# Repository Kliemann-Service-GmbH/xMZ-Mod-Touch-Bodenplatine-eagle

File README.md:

# xMZ-Mod-Touch
## Eagle Dateien Bodenplatine

## Howto's
### Material Listen (BOM) erstellen

Die Material Listen werden aus den Eagle Zeichnungen gewonnen. Hierzu werden in
Eagle zunächst über den "design link" alle Bauteile in der Farnell Datenbank
gesucht. Anschließend wird diese Liste gespeicherti (Design Link Export).

* Dateiname: "Deckelplatine $VERSION-order.txt"

Danach wird das bom.ulp in Eagle ausgeführt. Folgende Einstellungen sind zu
wählen:

	Listen-Typ: Werte (Häckchen unter "Attribute auflisten" setzen)
	Ausgabeformat: CSV

Diese Datei wird ebenfalls gespeichert.

* Dateiname: "Deckelplatine $VERSION BOM.csv"

### Farnell BOM Import

Farnell bietet die Möglichkeit über eine Web GUI die BOM Daten in eine
Bestellung umzuwandeln.

Format der CSV Datei für den Import:
- 3 Spalten ("Anzahl;	Ordercode; Beschreibung")
- Dateiformat .xlsx oder .xls

#Produktionsdaten
## Dokumentation Boardlayout Dateien

Einige der wichtigsten Ebenen (Drill, Solder, Paste) wurden einzeln zusammen
mit der "Document" Ebene (Layer 48) als PDF gedruckt (Siehe Script generate_documentaiont.scr).
Dieses PDF kann mit dem Ghostscript tool `gs` in ein PDF gewandelt werden.

```
cd doc

gs -dBATCH -dNOPAUSE -q -sDEVICE=pdfwrite -sOutputFile=Bodenplatine.pdf \
Bodenplatine-DIMENSIONS.pdf \
Bodenplatine-BOM.pdf \
Bodenplatine-Placement_TOP.pdf \
Bodenplatine-TOP.pdf \
Bodenplatine-BOTTOM.pdf \
Bodenplatine-BOTTOM-Solder-Mask.pdf \
Bodenplatine-TOP-Paste-Mask.pdf \
Bodenplatine-Drill-Drawing.pdf \
```

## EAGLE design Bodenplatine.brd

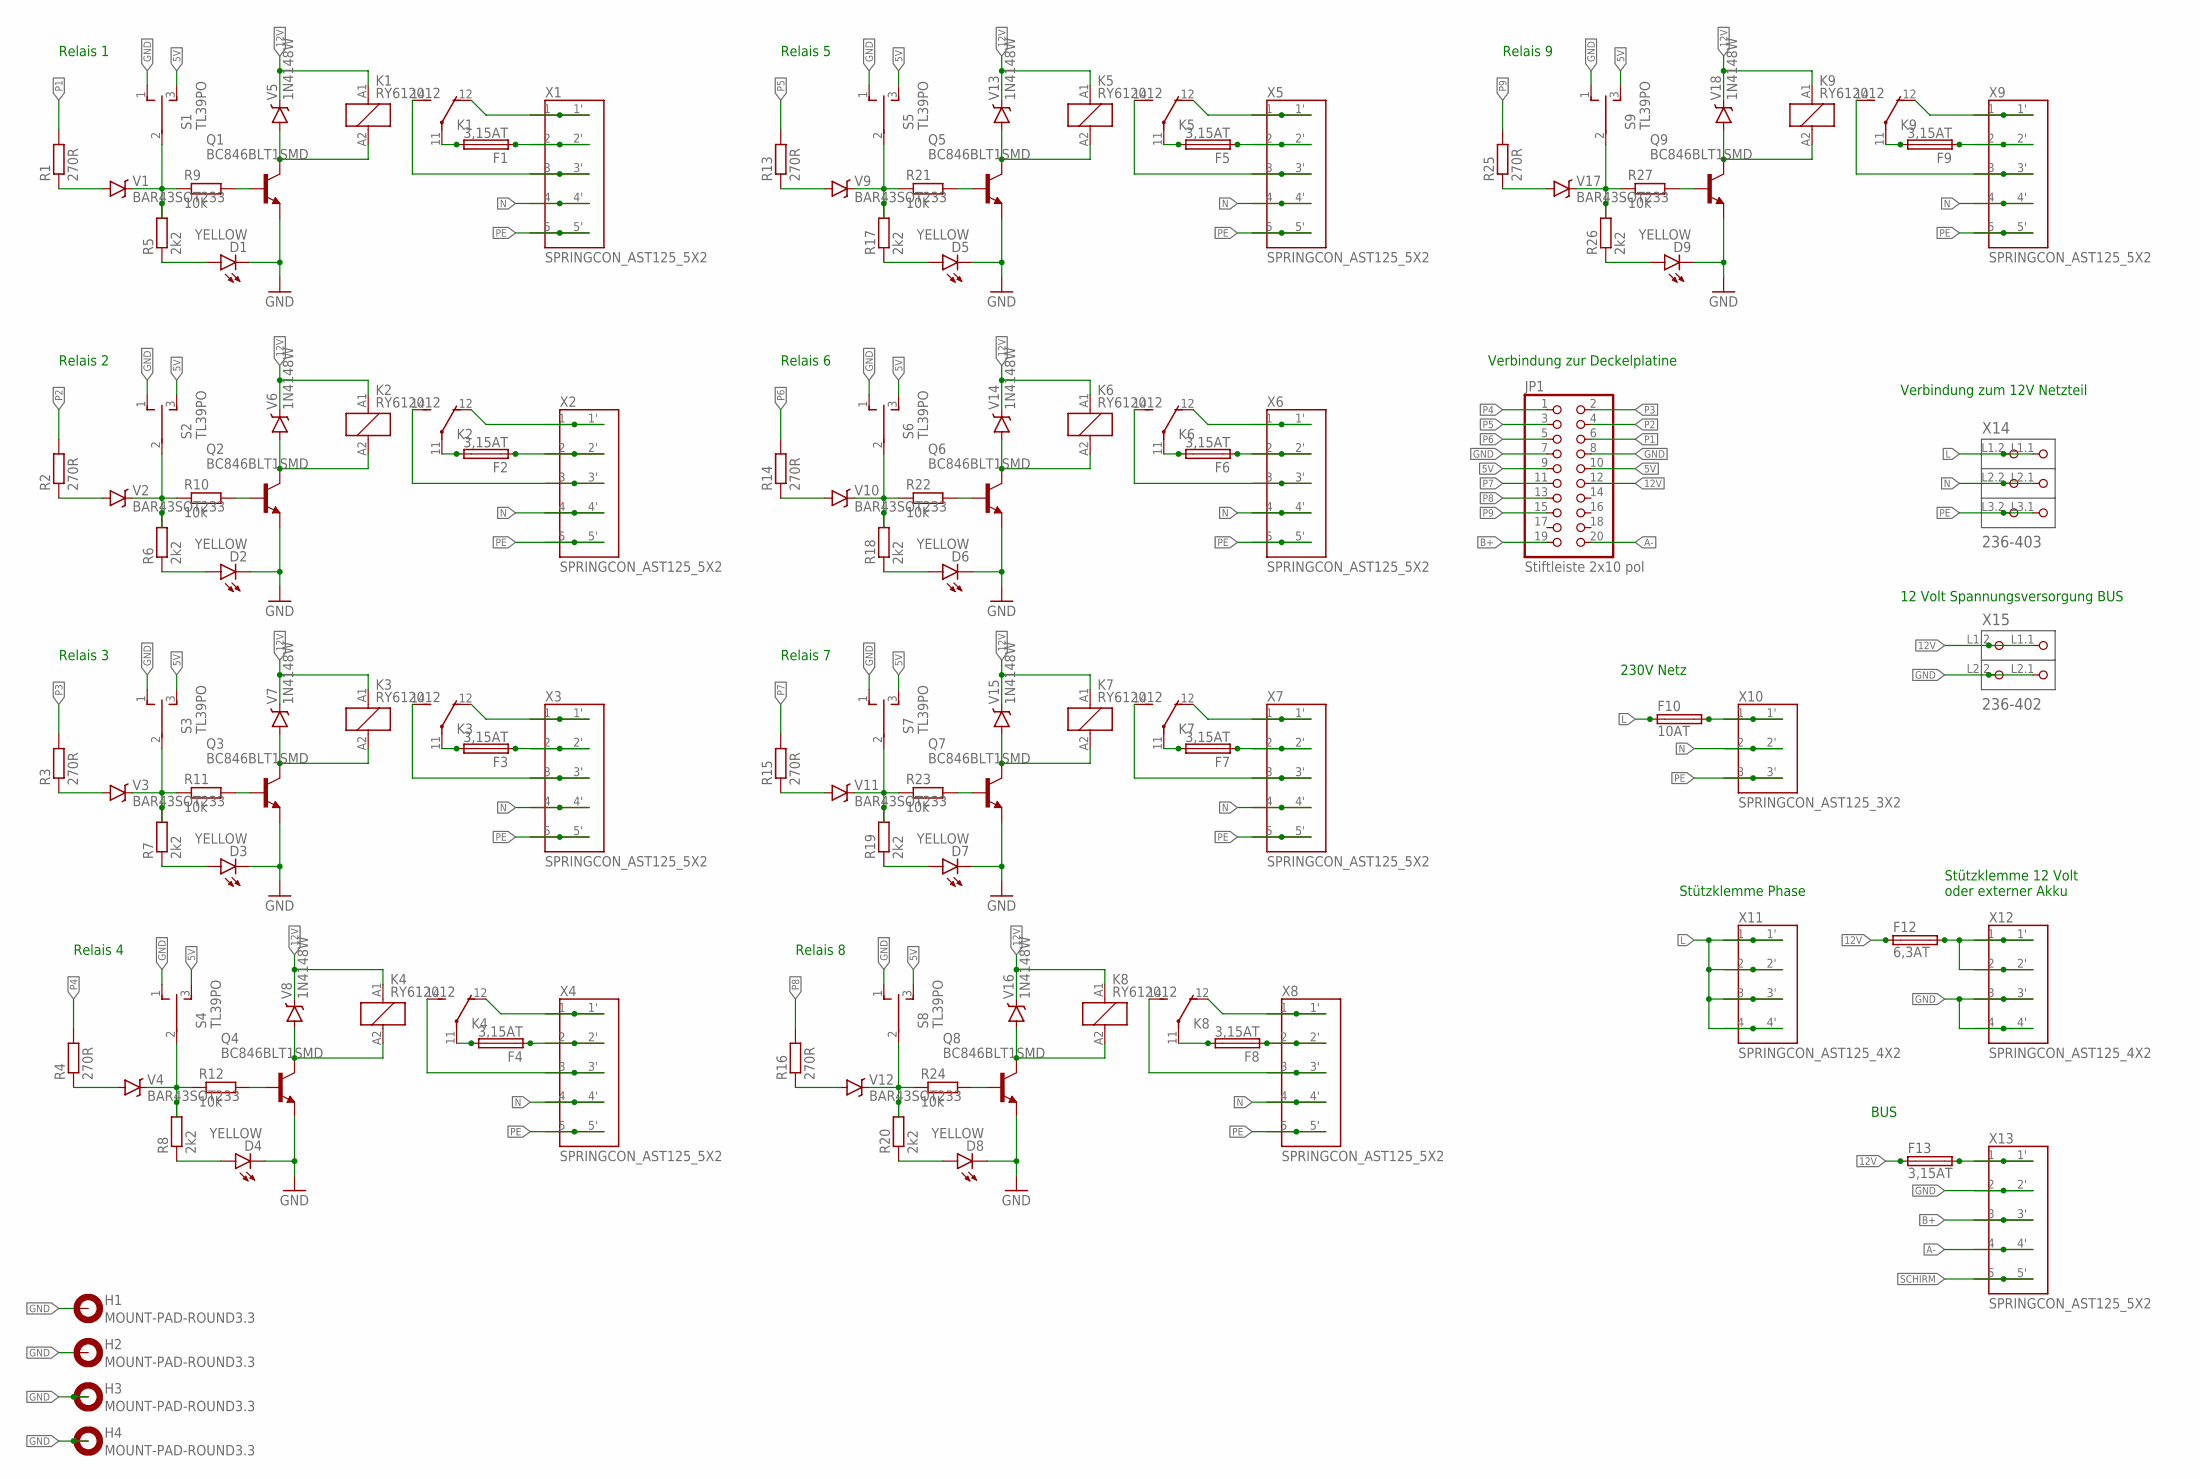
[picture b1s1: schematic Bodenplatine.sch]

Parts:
D1, D2, D3, D4, D5, D6, D7, D8, D9: YELLOW; LED-1206; MPN KP-3216SYC
F1, F2, F3, F4, F5, F6, F7, F8, F9, F13: 3,15AT; FPG4; MPN 3101.0040
F10: 10AT; FPG4; MPN 3101.0040
F12: 6,3AT; FPG4; MPN 3101.0040
H1, H2, H3, H4: MOUNT-PAD-ROUND3.3; 3,3-PAD
JP1: Stiftleiste 2x10 pol; 2X10
K1, K2, K3, K4, K5, K6, K7, K8, K9: RY612012; RY-II; MPN V23061B1005A301
Q1, Q2, Q3, Q4, Q5, Q6, Q7, Q8, Q9: BC846BLT1SMD; SOT23; MPN BC846,215
R1, R2, R3, R4, R13, R14, R15, R16, R25: 270R; M0805; MPN MC01W08055270R
R5, R6, R7, R8, R17, R18, R19, R20, R26: 2k2; R0603; MPN MC0063W060352K2
R9, R10, R11, R12, R21, R22, R23, R24, R27: 10k; R0603; MPN CPF0603B10KE1
S1, S2, S3, S4, S5, S6, S7, S8, S9: TL39PO; TL3XPO; MPN A103SYCQ04
V1, V2, V3, V4, V9, V10, V11, V12, V17: BAR43SOT233; SOT23; MPN BAR43
V5, V6, V7, V8, V13, V14, V15, V16, V18: 1N4148W; MINIMELF; MPN LL4148-GS08
X1, X2, X3, X4, X5, X6, X7, X8, X9, X13: SPRINGCON_AST125_5X2
X10: SPRINGCON_AST125_3X2
X11, X12: SPRINGCON_AST125_4X2
X14: 236-403; P-236-403; MPN 236-403
X15: 236-402; P-236-402; MPN 236-402

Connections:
5V: JP1.9, JP1.10, S1.3 (S), S2.3 (S), S3.3 (S), S4.3 (S), S5.3 (S), S6.3 (S), S7.3 (S), S8.3 (S), S9.3 (S)
12V: F12.1, F13.1, JP1.12, K1.A1 (1), K2.A1 (1), K3.A1 (1), K4.A1 (1), K5.A1 (1), K6.A1 (1), K7.A1 (1), K8.A1 (1), K9.A1 (1), V5.C, V6.C, V7.C, V8.C, V13.C, V14.C, V15.C, V16.C, V18.C, X15.L1.1 (P1.1), X15.L1.2 (P1.2)
A-: JP1.20, X13.4, X13.4' (4)
B+: JP1.19, X13.3, X13.3' (3)
GND: D1.C, D2.C, D3.C, D4.C, D5.C, D6.C, D7.C, D8.C, D9.C, H1.B3,3, H2.B3,3, H3.B3,3, H4.B3,3, JP1.7, JP1.8, Q1.2 (E), Q2.2 (E), Q3.2 (E), Q4.2 (E), Q5.2 (E), Q6.2 (E), Q7.2 (E), Q8.2 (E), Q9.2 (E), S1.1 (O), S2.1 (O), S3.1 (O), S4.1 (O), S5.1 (O), S6.1 (O), S7.1 (O), S8.1 (O), S9.1 (O), X12.3, X12.3' (3), X12.4, X12.4' (4), X13.2, X13.2' (2), X15.L2.1 (P2.1), X15.L2.2 (P2.2)
L: F10.1, X11.1, X11.1' (1), X11.2, X11.2' (2), X11.3, X11.3' (3), X11.4, X11.4' (4), X14.L1.1 (P1.1), X14.L1.2 (P1.2)
N: X1.4, X1.4' (4), X2.4, X2.4' (4), X3.4, X3.4' (4), X4.4, X4.4' (4), X5.4, X5.4' (4), X6.4, X6.4' (4), X7.4, X7.4' (4), X8.4, X8.4' (4), X9.4, X9.4' (4), X10.2, X10.2' (2), X14.L2.1 (P2.1), X14.L2.2 (P2.2)
unnamed: F2.1, X2.2, X2.2' (2)
unnamed: K2.14 (S), X2.3, X2.3' (3)
unnamed: F2.2, K2.11
unnamed: K2.12 (O), X2.1, X2.1' (1)
unnamed: K2.A2 (2), Q2.3 (C), V6.A
unnamed: K3.14 (S), X3.3, X3.3' (3)
unnamed: R2.1, V2.1 (A)
unnamed: R6.2, R10.1, S2.2, V2.3 (C)
unnamed: D2.A, R6.1
unnamed: Q2.1 (B), R10.2
unnamed: F3.2, K3.11
unnamed: R3.1, V3.1 (A)
unnamed: R7.2, R11.1, S3.2, V3.3 (C)
unnamed: D3.A, R7.1
unnamed: Q3.1 (B), R11.2
unnamed: K3.A2 (2), Q3.3 (C), V7.A
unnamed: F3.1, X3.2, X3.2' (2)
unnamed: K3.12 (O), X3.1, X3.1' (1)
unnamed: K4.14 (S), X4.3, X4.3' (3)
unnamed: F4.2, K4.11
unnamed: R4.1, V4.1 (A)
unnamed: R8.2, R12.1, S4.2, V4.3 (C)
unnamed: D4.A, R8.1
unnamed: Q4.1 (B), R12.2
unnamed: K4.A2 (2), Q4.3 (C), V8.A
unnamed: F4.1, X4.2, X4.2' (2)
unnamed: K4.12 (O), X4.1, X4.1' (1)
unnamed: K5.14 (S), X5.3, X5.3' (3)
unnamed: F5.2, K5.11
unnamed: R13.1, V9.1 (A)
unnamed: R17.2, R21.1, S5.2, V9.3 (C)
unnamed: D5.A, R17.1
unnamed: Q5.1 (B), R21.2
unnamed: K5.A2 (2), Q5.3 (C), V13.A
unnamed: F5.1, X5.2, X5.2' (2)
unnamed: K5.12 (O), X5.1, X5.1' (1)
unnamed: K6.14 (S), X6.3, X6.3' (3)
unnamed: F6.2, K6.11
unnamed: R14.1, V10.1 (A)
unnamed: R18.2, R22.1, S6.2, V10.3 (C)
unnamed: D6.A, R18.1
unnamed: Q6.1 (B), R22.2
unnamed: K6.A2 (2), Q6.3 (C), V14.A
unnamed: F6.1, X6.2, X6.2' (2)
unnamed: K6.12 (O), X6.1, X6.1' (1)
unnamed: K7.14 (S), X7.3, X7.3' (3)
unnamed: F7.2, K7.11
unnamed: R15.1, V11.1 (A)
unnamed: R19.2, R23.1, S7.2, V11.3 (C)
unnamed: D7.A, R19.1
unnamed: Q7.1 (B), R23.2
unnamed: K7.A2 (2), Q7.3 (C), V15.A
unnamed: F7.1, X7.2, X7.2' (2)
unnamed: K7.12 (O), X7.1, X7.1' (1)
unnamed: K8.14 (S), X8.3, X8.3' (3)
unnamed: F8.2, K8.11
unnamed: R16.1, V12.1 (A)
unnamed: R20.2, R24.1, S8.2, V12.3 (C)
unnamed: D8.A, R20.1
unnamed: Q8.1 (B), R24.2
unnamed: K8.A2 (2), Q8.3 (C), V16.A
unnamed: F8.1, X8.2, X8.2' (2)
unnamed: K8.12 (O), X8.1, X8.1' (1)
unnamed: K9.14 (S), X9.3, X9.3' (3)
unnamed: F9.2, K9.11
unnamed: R25.1, V17.1 (A)
unnamed: R26.2, R27.1, S9.2, V17.3 (C)
unnamed: D9.A, R26.1
unnamed: Q9.1 (B), R27.2
unnamed: K9.A2 (2), Q9.3 (C), V18.A
unnamed: F9.1, X9.2, X9.2' (2)
unnamed: K9.12 (O), X9.1, X9.1' (1)
unnamed: K1.14 (S), X1.3, X1.3' (3)
unnamed: F1.2, K1.11
unnamed: R1.1, V1.1 (A)
unnamed: R5.2, R9.1, S1.2, V1.3 (C)
unnamed: D1.A, R5.1
unnamed: Q1.1 (B), R9.2
unnamed: K1.A2 (2), Q1.3 (C), V5.A
unnamed: F1.1, X1.2, X1.2' (2)
unnamed: K1.12 (O), X1.1, X1.1' (1)
unnamed: F10.2, X10.1, X10.1' (1)
unnamed: F13.2, X13.1, X13.1' (1)
unnamed: F12.2, X12.1, X12.1' (1), X12.2, X12.2' (2)
P1: JP1.6, R1.2
P2: JP1.4, R2.2
P3: JP1.2, R3.2
P4: JP1.1, R4.2
P5: JP1.3, R13.2
P6: JP1.5, R14.2
P7: JP1.11, R15.2
P8: JP1.13, R16.2
P9: JP1.15, R25.2
PE: X1.5, X1.5' (5), X2.5, X2.5' (5), X3.5, X3.5' (5), X4.5, X4.5' (5), X5.5, X5.5' (5), X6.5, X6.5' (5), X7.5, X7.5' (5), X8.5, X8.5' (5), X9.5, X9.5' (5), X10.3, X10.3' (3), X14.L3.1 (P3.1), X14.L3.2 (P3.2)
SCHIRM: X13.5, X13.5' (5)

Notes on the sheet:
Relais 2
Relais 3
Relais 4
Relais 5
Relais 6
Relais 7
Relais 8
Relais 9
Relais 1
Verbindung zur Deckelplatine
230V Netz
Stützklemme Phase
Stützklemme 12 Volt oder externer Akku
BUS
Verbindung zum 12V Netzteil
12 Volt Spannungsversorgung BUS

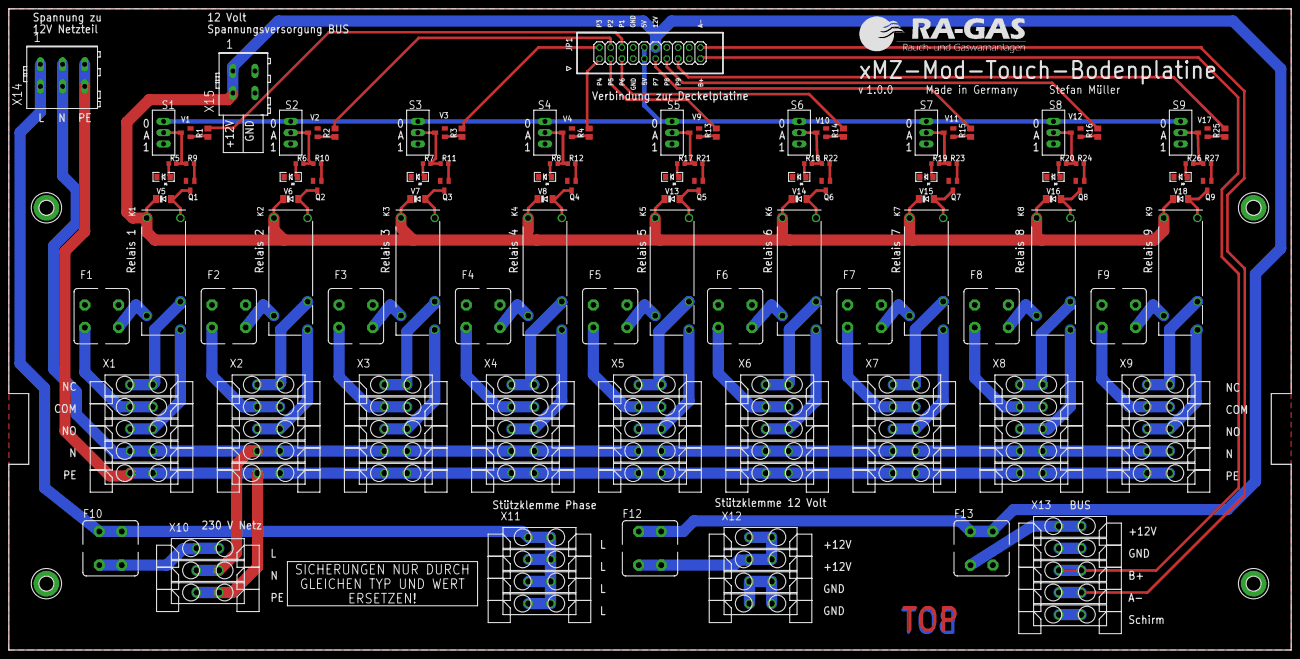
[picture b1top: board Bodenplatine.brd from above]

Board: 2 copper layers, 290.0 x 145.0 mm, 118 parts (0 on the bottom side), 102 nets.

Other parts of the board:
DRILEGEND: DRILEGEND
U$1: TEXT_FUSE
U$2: TEXT_NAME_VERSION_AUTHOR
U$3: LOGO_RA-GAS
U$5: A3-LOC-RA-GAS

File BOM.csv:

Qty,Value,Device,Package,Parts,Description,MF,MPN,DATASHEETURL,OC_CONRAD,OC_FARNELL,PROD_ID,VALUE
9,10k,R-EU_R0603,R0603,"R9, R10, R11, R12, R21, R22, R23, R24, R27","RESISTOR, European s",TE CONNECTIVITY / NEOHM,CPF0603B10KE1,http://www.farnell.com/datasheets/1786677.pdf,,1697388,,
9,1N4148W,LL4148,MINIMELF,"V5, V6, V7, V8, V13, V14, V15, V16, V18",VISHAY  LL4148-GS08 ,VISHAY,LL4148-GS08,http://www.farnell.com/datasheets/1353494.pdf,,9549986,,
9,270R,R-EU_M0805,M0805,"R1, R2, R3, R4, R13, R14, R15, R16, R25","RESISTOR, European s",MULTICOMP,MC01W08055270R,http://www.farnell.com/datasheets/1716700.pdf,,9334254,,
9,2k2,R-EU_R0603,R0603,"R5, R6, R7, R8, R17, R18, R19, R20, R26","RESISTOR, European s",MULTICOMP,MC0063W060352K2,http://www.farnell.com/datasheets/1788326.pdf,,9331913,,
9,BAR43SOT233,BAR43SOT233,SOT23,"V1, V2, V3, V4, V9, V10, V11, V12, V17",FAIRCHILD SEMICONDUC,FAIRCHILD SEMICONDUCTOR,BAR43,http://www.farnell.com/datasheets/1963228.pdf,,2453275,,
9,BC846BLT1SMD,BC846BLT1SMD,SOT23,"Q1, Q2, Q3, Q4, Q5, Q6, Q7, Q8, Q9",NPN Transistor,NXP,"BC846,215",http://www.farnell.com/datasheets/1699731.pdf,,1081227,,
4,MOUNT-PAD-ROUND3.3,MOUNT-PAD-ROUND3.3,"3,3-PAD","H1, H2, H3, H4","MOUNTING PAD, round",,,,,unknown,,
9,YELLOW,LED-YELLOWLARGE,LED-1206,"D1, D2, D3, D4, D5, D6, D7, D8, D9",Yellow SMD LEDs,KINGBRIGHT,KP-3216SYC,http://www.farnell.com/datasheets/55733.pdf,,8529990,DIO-00820,YELLOW

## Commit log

2016-02-25 Erste .gitignore Version
    Diese Version ignoriert die Eagle Sicherungskopien.
2016-02-25 Import Version v0.9.0 (v0.0.1)
    Aus dieser Version wurde der erste Prototyp von 'Conrad
    Leiterplattenservice' produziert. Der Aufdruck war leider v0.0.1, die
    richtige Versionsnummer lautete aber v0.9.0.
2016-02-25 Import der Version v0.9.5
    Aus dieser Version wurde der zweite Prototype erstellt. Der Produzent
    war dieses Mal https://portal.multi-circuit-boards.eu
2016-02-26 Anschluss Deckelplatine gegen verdrehen gesichert
2016-03-07 Erste Version eines Scripts welches div. Layer mit einem Frame druckt
2016-03-07 Erste Version der 1.0.0 Produktionsdaten
    Versuch alle Datenblätter, eine Kalkulation und Lagerverwaltung und
    einer Eagle Datei mit "nur SMD" Bestückungsvariante. Zur Zeit noch nicht
    fertig.
2016-03-07 Produktionsdaten exportiert. v1.0.0 soweit fertig
2016-03-09 Kleine Aenderungen an der README
2016-08-15 Produktionsdaten und BOM.csv eingebunden
